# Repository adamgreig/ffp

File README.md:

# FFP: Flash/FPGA Programmer

FFP is a dead-simple USB to bidirectional SPI bridge for programming iCE40
FPGAs and SPI flashes. The hardware is an STM32F042 and not much else.
Firmware and host software is written in Rust.

The firmware additionally supports SWD via the CMSIS-DAP v1 and v2 protocols,
so many debuggers such as [probe-rs], [OpenOCD], and [pyOCD] are able to
use an FFP to debug and program Cortex-M and other microcontrollers.

[probe-rs]: https://probe.rs
[OpenOCD]: http://openocd.org
[pyOCD]: https://github.com/mbedmicro/pyOCD

See [software/](software/) for the host-side software, [firmware/](firmware/)
for the embedded device firmware, and [hardware/](hardware/ffp/) for the
hardware design files.

## Pinout

The FFP r1 hardware uses a 5x2 pin 0.05"-pitch connector, which is also
commonly used for Cortex family microcontrollers for SWD and JTAG. The pinout
is deliberately compatible (though note `RESET` is moved) to allow hardware
reuse and for compatibility with tools such as TagConnect cables.

```ascii
          ______
    3v3 --|1  2|-- FLASH DI / FPGA DO / SWDIO
    GND --|3  4|-- CLK / SWCLK
    GND --|5  6|-- CS / SWO
        x-|7  8|-- FPGA nRST
    GND --|9 10|-- FLASH DO / FPGA DI / nRESET
          ------

```

This is the same pinout used by
[amp_flashprog](https://github.com/adamgreig/amp_flashprog), a custom firmware
for [Black Magic Probes](https://github.com/blacksphere/blackmagic) to bitbang
SPI to the same ends.

## Licence

Software and firmware is licensed under either of

* Apache License, Version 2.0 ([LICENSE-APACHE](LICENSE-APACHE) or
  http://www.apache.org/licenses/LICENSE-2.0)
* MIT license ([LICENSE-MIT](LICENSE-MIT) or http://opensource.org/licenses/MIT)

at your option.

Hardware design files are licensed under the Creative Commons Attribution
license ([CC-BY](https://creativecommons.org/licenses/by/4.0/)).

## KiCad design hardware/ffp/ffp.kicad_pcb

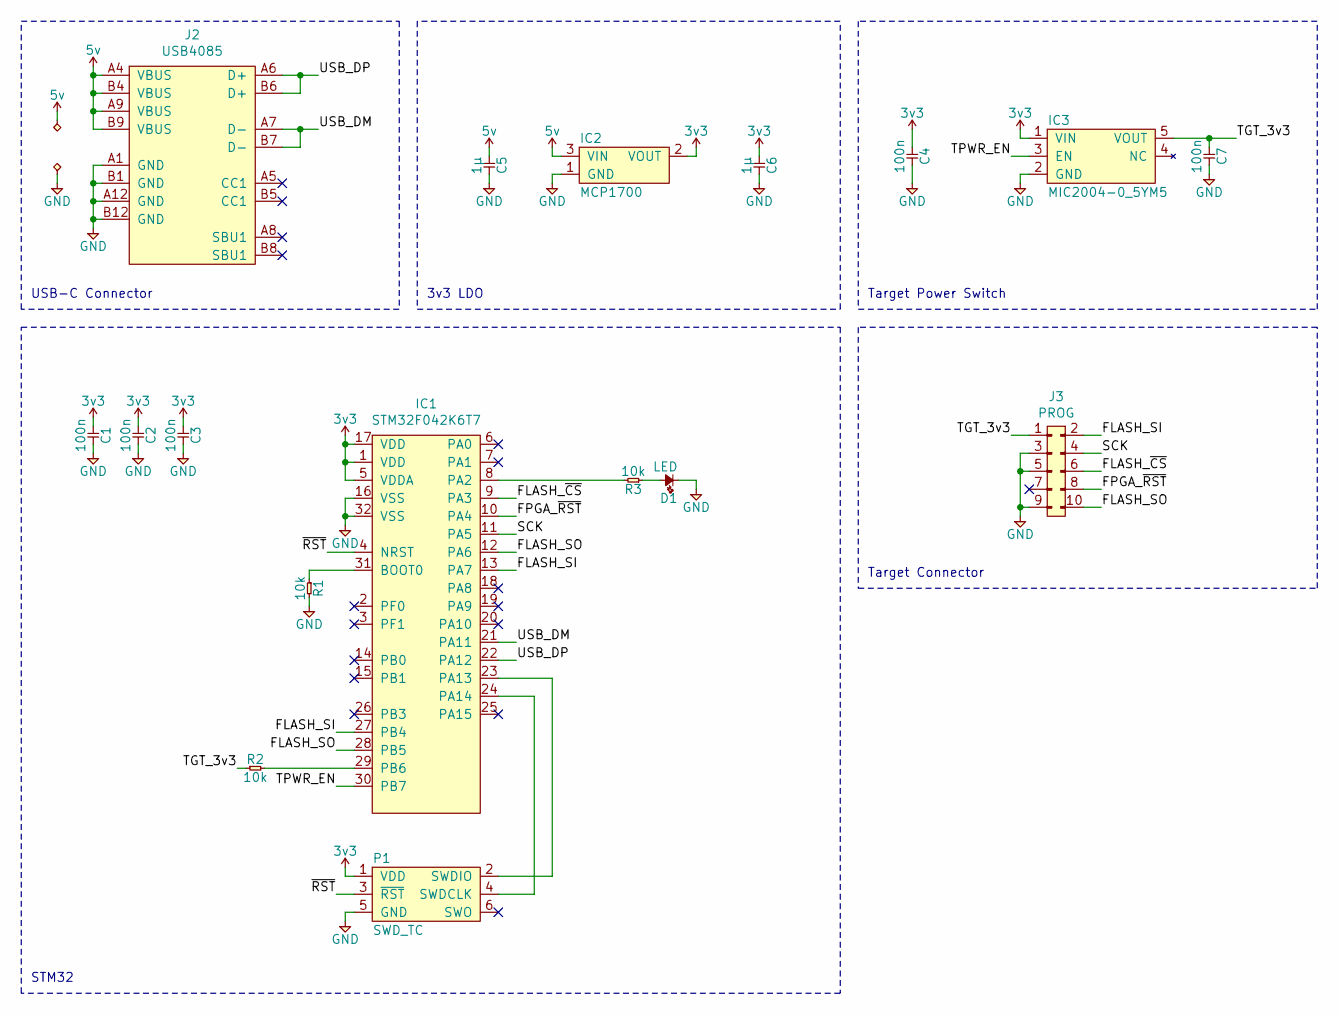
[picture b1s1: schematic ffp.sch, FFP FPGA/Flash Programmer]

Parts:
C1, C2, C3, C4, C7: 100n; 0603; Farnell 1759122
C5, C6: 1µ; 0603; Farnell 2768389
D1: LED; 0603-LED; Farnell 2610409
IC1: STM32F042K6T7; LQFP-32; Farnell 2469553
IC2: MCP1700; SOT-23; Farnell 1296592
IC3: MIC2004-0_5YM5; SOT-23-5; Farnell 2509877
J2: USB4085; Farnell 2924867
J3: PROG; FTSH-105-01-L-DV-K; Farnell 2856437
P1: SWD_TC; TC2030-NL
R1, R2, R3: 10k; 0603; Farnell 2447230

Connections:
3v3: C1.1, C2.1, C3.1, C4.1, C6.1, IC1.1 (VDD), IC1.5 (VDDA), IC1.17 (VDD), IC2.2 (VOUT), IC3.1 (VIN), P1.1 (VDD)
5v: C5.1, IC2.3 (VIN), J2.A4 (VBUS), J2.A9 (VBUS), J2.B4 (VBUS), J2.B9 (VBUS)
/FLASH_SI: IC1.13 (PA7), IC1.27 (PB4), J3.2
/FLASH_SO: IC1.12 (PA6), IC1.28 (PB5), J3.10
/FLASH_~CS: IC1.9 (PA3), J3.6
/FPGA_~RST: IC1.10 (PA4), J3.8
/SCK: IC1.11 (PA5), J3.4
/TGT_3v3: C7.1, IC3.5 (VOUT), J3.1, R2.1
/TPWR_EN: IC1.30 (PB7), IC3.3 (EN)
/USB_DM: IC1.21 (PA11), J2.A7 (D-), J2.B7 (D-)
/USB_DP: IC1.22 (PA12), J2.A6 (D+), J2.B6 (D+)
/~RST: IC1.4 (NRST), P1.3 (~RST)
GND: C1.2, C2.2, C3.2, C4.2, C5.2, C6.2, C7.2, D1.1, IC1.16 (VSS), IC1.32 (VSS), IC2.1 (GND), IC3.2 (GND), J2.A1 (GND), J2.A12 (GND), J2.B1 (GND), J2.B12 (GND), J3.3, J3.5, J3.9, P1.5 (GND), R1.2
unnamed: D1.2, R3.1
unnamed: IC1.8 (PA2), R3.2
unnamed: IC1.23 (PA13), P1.2 (SWDIO)
unnamed: IC1.24 (PA14), P1.4 (SWDCLK)
unnamed: IC1.29 (PB6), R2.2
unnamed: IC1.31 (BOOT0), R1.1

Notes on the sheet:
USB-C Connector
3v3 LDO
Target Power Switch
Target Connector
STM32

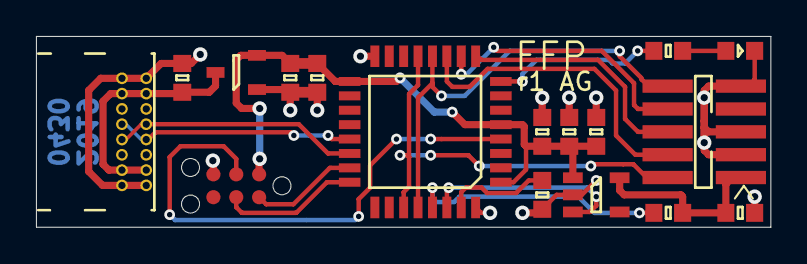
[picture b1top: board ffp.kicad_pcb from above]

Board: 2 copper layers, 40.8 x 10.6 mm, 17 parts (0 on the bottom side), 19 nets.

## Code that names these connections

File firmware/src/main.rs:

// Copyright 2019 Adam Greig
// Dual licensed under the Apache 2.0 and MIT licenses.

#![no_std]
#![no_main]

extern crate panic_halt;
use cortex_m_rt::{entry, pre_init};
use git_version::git_version;

const GIT_VERSION: &str = git_version!();

pub mod hal;
pub mod app;
pub mod swd;
pub mod dap;
pub mod jtag;

#[pre_init]
unsafe fn pre_init() {
    // Check if we should jump to system bootloader.
    //
    // When we receive the BOOTLOAD command over USB,
    // we write a flag to a static and reset the chip,
    // and `bootload::check()` will jump to the system
    // memory bootloader if the flag is present.
    //
    // It must be called from pre_init as otherwise the
    // flag is overwritten when statics are initialised.
    hal::bootload::check();
}

#[entry]
fn main() -> ! {
    let flash = hal::flash::Flash::new(stm32ral::flash::Flash::take().unwrap());
    let rcc = hal::rcc::RCC::new(stm32ral::rcc::RCC::take().unwrap(),
                                 stm32ral::crs::CRS::take().unwrap());
    let nvic = hal::nvic::NVIC::new(stm32ral::nvic::NVIC::take().unwrap(),
                                    stm32ral::scb::SCB::take().unwrap());
    let dma = hal::dma::DMA::new(stm32ral::dma1::DMA1::take().unwrap());
    let gpioa = hal::gpio::GPIO::new(stm32ral::gpio::GPIOA::take().unwrap());
    let gpiob = hal::gpio::GPIO::new(stm32ral::gpio::GPIOB::take().unwrap());
    let spi = hal::spi::SPI::new(stm32ral::spi::SPI1::take().unwrap());
    let mut uart = hal::uart::UART::new(stm32ral::usart::USART2::take().unwrap(), &dma);
    let mut usb = hal::usb::USB::new(stm32ral::usb::USB::take().unwrap());

    // Define pinout.
    // Some pins are defined early so we can memoise their modes for
    // faster mode switching at runtime.
    let sck = gpioa.pin(5);
    let flash_si = gpioa.pin(7);
    let flash_si_input_mode = flash_si.memoise_mode_input();
    let flash_si_alternate_mode = flash_si.memoise_mode_alternate();
    let sck_output_mode = sck.memoise_mode_output();
    let sck_alternate_mode = sck.memoise_mode_alternate();
    let pins = hal::gpio::Pins {
        led: gpioa.pin(2),
        cs: gpioa.pin(3),
        fpga_rst: gpioa.pin(4),
        sck,
        flash_so: gpioa.pin(6),
        flash_si,
        fpga_so: gpiob.pin(4),
        fpga_si: gpiob.pin(5),
        tpwr_det: gpiob.pin(6),
        tpwr_en: gpiob.pin(7),

        flash_si_input_mode,
        flash_si_alternate_mode,
        sck_output_mode,
        sck_alternate_mode,
    };

    let swd = swd::SWD::new(&spi, &pins);
    let jtag = jtag::JTAG::new(&pins);
    let mut dap = dap::DAP::new(swd, &jtag, &mut uart, &pins);

    // Create App instance with the HAL instances
    let mut app = app::App::new(
        &flash, &rcc, &nvic, &dma, &pins, &spi, &jtag, &mut usb, &mut dap);

    // Initialise application, including system peripherals
    app.setup();

    loop {
        // Process events
        app.poll();
    }
}

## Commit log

2019-04-30 r1 of ffp hardware
2019-05-01 Tidy schematic and render PDF
2019-05-05 Update datasheet for stm32f0
2019-05-06 Start work on firmware
2019-05-06 More USB stuff
2019-05-07 more various work on usb
2019-05-07 Add photo of PCB
2019-05-08 Working USB enumeration on real hardware
2019-05-08 Toggle LED based on SetCS request
2019-05-08 Minor tidyups
2019-05-08 Add bootload request
2019-05-08 Add note about option bytes to firmware readme
2019-05-08 Update memory.x to prevent loading USBSRAM
2019-05-08 Use a normal static and pre_init instead of writing to backup registers
2019-05-08 Generate string descriptors on the fly from &str
2019-05-08 Swap to single main loop instead of interrupts
    This allows storing state inside the HAL drivers (since they no longer
    need to be able to be "stolen" by the ISRs), removes all `steal()`
    methods, and should simplify the rest of the application logic (dealing
    with events coming to/from the USB).
    We can use WFE and SEVONPEND to continue to sleep until an interrupt
    occurs. Increased response latency should be negligable so long as we
2019-05-09 Remove LED handling from usb HAL
2019-05-09 Refactor main into new App struct, start implementing vendor requests
2019-05-09 Working USB bulk transfer loopback
2019-05-09 Some tidyups and unsafe improvements
2019-05-09 Make access to BTABLE and EPxBUF safe inside USB
2019-05-09 Add application-level suspend handling
2019-05-10 Correct use of COUNT_RX field
2019-05-10 Start work on Rust application
2019-05-12 Add ToBytes trait to Descriptors
2019-05-12 Add basic SPI support with blocking DMA transfers
2019-05-13 Remove unneeded LDMA setting
2019-05-13 Rename USB::{enable,disable}_rx to {enable,disable}_data_rx
2019-05-13 Handle non-64-byte data transfers
2019-05-13 Add pullup to CS
2019-05-14 Add prog.py from amp_flashprog modified for ffp
2019-05-15 Release under open-source licences
2019-05-15 Add updated schematic pdf and PCB png
2019-05-22 Swap to newly-assigned USB PID FF50
2019-06-10 Add bootload and udev details
2019-06-10 Improve udev rules
2019-06-11 Start work on Rust port of programming script
2019-06-11 Only send 8 dummy clocks, not 16
2019-06-13 Software more or less feature-complete
2019-06-13 Add command line output and timer
2019-06-13 Fix time display
2019-06-13 Update READMEs
2019-06-13 Update driver link in readme
2019-06-13 Add bootload command
2019-06-13 Set high-z mode on exit, along with turning off LED
2019-06-14 Report device unique ID as USB serial number
2019-06-14 Update ffp software to support multiple FFP devices
2019-11-08 Update firmware README to use ffp bootload command
2020-04-03 Update dependencies
2020-04-03 successfully read/write memory
2020-04-03 memoise swd mode swaps to speed them up a bit
2020-04-03 Experiments in SWD
2020-04-03 Fix RDATA parity and other tidyups
2020-04-03 further development, swd wrapper, many small speedups
2020-04-03 start working on CMSIS-DAP support: add HID interface and descriptors
2020-04-03 update main to still run usb
2020-04-03 Get HID report working, device is recongised as a CMSIS-DAP probe!
2020-04-03 Swap to num_enum instead of hand-written conversions
2020-04-03 Remove handling for >64byte control transfers since we actually _just_ fit as it stands
2020-04-06 Major refactor of USB stack to split core stack and individual endpoints
2020-04-07 Working CMSIS-DAP support!
2020-04-07 Tidy up
2020-04-07 Update README for DAP/SWD
2020-04-11 Update note in README about bootloader option bit
2020-04-11 Have the firmware take care of option programming
    * Also update README accordingly
    * Closes #7
2020-04-11 Add more detailed build instructions to README. Closes #8
2020-04-12 Re-implement sending control data longer than 64 bytes.
    This effectively reverts 1dee501d522e7fae2124533de5eafc2261450c89.
    We can now send up to 320 byte control responses, which allows for
    longer descriptors and strings, but crucially also causes us to send
    ZLPs after an exactly 64-byte transfer, fixing a failure to enumerate
    on Windows.
    Closes #9.
2020-04-12 Update READMEs with more details on building and flashing firmware and software and on Windows drivers
2020-04-12 Update bootloading instructions further
2020-04-13 Swap from libusb to rusb crate. Closes #12
2020-04-13 Add Windows OS Feature descriptors for automatic WinUSB support including CMSIS-DAP v2 Interface GUID
2020-04-14 Add CMSIS-DAPv2 support with bulk endpoints. Closes #6
2020-04-14 Handle posted AP reads in transfer_block better. Closes #3
2020-04-14 Default SWD clock to 1.5MHz
2020-04-15 Add instructions for cross-compiling to Windows
2020-04-15 Add instructions to create a DfuSe file with dfu-tool
2020-04-20 Appease clippy
2020-04-20 Try adding CI
2020-04-20 CI broken because GHA can't set a working directory, sigh
2020-04-20 Install thumb target in CI
2020-04-20 Test building release images in CI
2020-04-20 Fix release.yaml
2020-04-20 Retry windows build
2020-04-20 Retry firmware bootloader image build
2020-04-20 Try windows 32-bit build
2020-04-20 Mark v1.3.0 of firmware; swap release workflow to releases only
2020-04-20 Fix release workflow syntax
2020-04-20 Add note about pre-built binaries to READMEs
2020-04-25 Add first go at SWO support, via DAP commands only
2020-04-26 Implement SWO streaming over dedicated EP. Closes #5
2020-04-26 Firmware version 1.3.1, adding SWO support
2020-04-26 Update README to include new CMSIS-DAP v2 support
2020-05-05 Very simple demo impl of DMA traits
2020-07-23 Allow asserting reset before connecting in DAP mode
2020-07-24 Enforce maximum DAP_SWJ_Pins wait value of 3s
2020-07-24 Don't force nRESET high when swapping to swd_mode in case it's already been set low
2020-07-24 Set nRESET high at boot and after SWD disconnect
2020-07-24 Firmware version 1.3.2, fix bug in reset pin handling before connecting
2020-07-24 Add LTO to software build to hopefully help i686 Windows builds
2020-08-03 First go at JTAG mode, implementing DAP_JTAG_Sequence
2020-08-17 Simplify method names on SequenceBuilder
2020-08-18 First go at ECP5 support
2020-08-19 Working JTAG ECP5 SPI passthrough, can read attached SPI flash
2020-08-19 Add inline-asm feature and assembly version of jtag::transfer_rw for 3x speedup
2020-09-30 Support DAP_JTAG_Sequence command
2020-10-08 Mark JTAG as supported in capabilities
2020-10-12 Add DFU interface to support rebooting into bootloader
2020-10-12 Temporarily remove idcode check as it leaves tap in unhelpful state
2020-10-26 Zero JTAG result buffer before writing to it
2020-10-26 Add note about using dfu-util to enter bootloader mode
2020-11-25 Fix not setting nRST back to 1
2021-01-03 Remove JTAG features from software (ported to ecpdap)
2021-01-21 Fix memory.x for new c-m-rt
2021-01-25 Use new cortex-m 0.7 bootload method

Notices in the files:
hardware/ffp/ffp.kicad_pcb:
Licensed under Creative Commons Attribution 4.0
